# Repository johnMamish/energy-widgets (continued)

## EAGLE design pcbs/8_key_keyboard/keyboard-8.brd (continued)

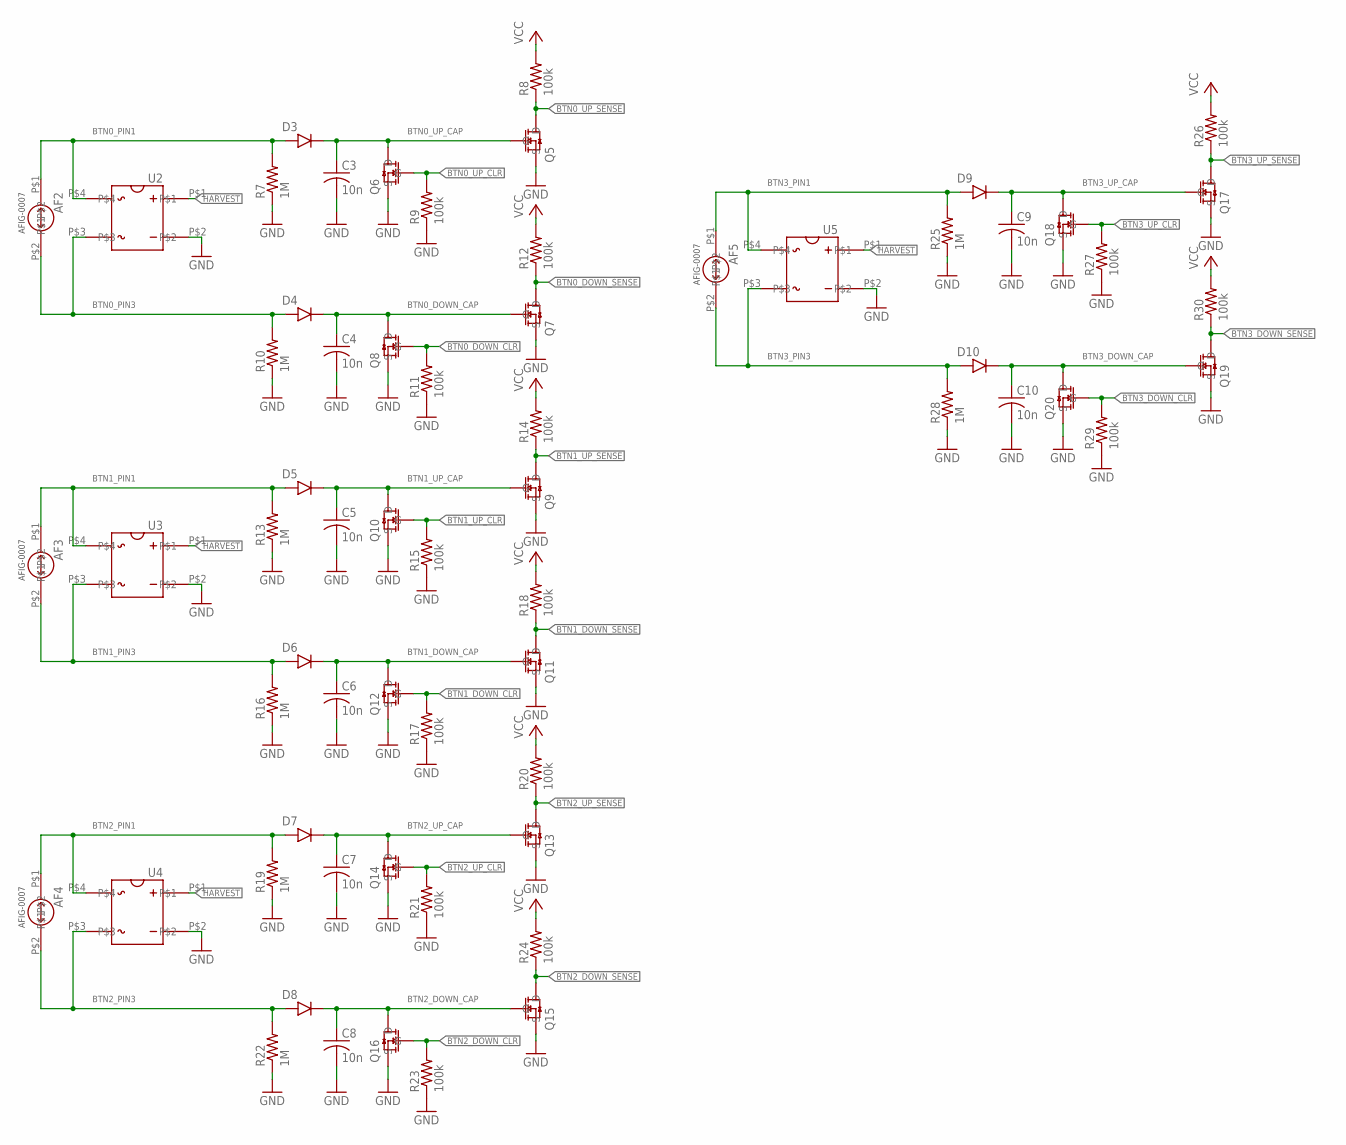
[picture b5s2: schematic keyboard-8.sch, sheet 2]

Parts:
AF2, AF3, AF4, AF5: BUTTON-MOUNT
C3, C4, C5, C6, C7, C8, C9, C10: 10n; C0402
D3, D4, D5, D6, D7, D8, D9, D10: DFLU1200
Q5, Q7, Q9, Q11, Q13, Q15, Q17, Q19: 2N7002K-7
Q6, Q8, Q10, Q12, Q14, Q16, Q18, Q20: BSS138K
R7, R10, R13, R16, R19, R22, R25, R28: 1M; R0402
R8, R9, R11, R12, R14, R15, R17, R18, R20, R21, R23, R24, R26, R27, R29, R30: 100k; R0402
U2, U3, U4, U5: CDBHD140L-G; CDBHDXX0L-G

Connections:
BTN0_DOWN_CAP: C4.1, D4.K, Q7.G, Q8.D
BTN0_DOWN_CLR: Q8.G, R11.2; also elsewhere on the board
BTN0_DOWN_SENSE: Q7.D, R12.1; also elsewhere on the board
BTN0_PIN1: AF2.P$1, D3.A, R7.2, U2.P$4
BTN0_PIN3: AF2.P$2, D4.A, R10.2, U2.P$3
BTN0_UP_CAP: C3.1, D3.K, Q5.G, Q6.D
BTN0_UP_CLR: Q6.G, R9.2; also elsewhere on the board
BTN0_UP_SENSE: Q5.D, R8.1; also elsewhere on the board
BTN1_DOWN_CAP: C6.1, D6.K, Q11.G, Q12.D
BTN1_DOWN_CLR: Q12.G, R17.2; also elsewhere on the board
BTN1_DOWN_SENSE: Q11.D, R18.1; also elsewhere on the board
BTN1_PIN1: AF3.P$1, D5.A, R13.2, U3.P$4
BTN1_PIN3: AF3.P$2, D6.A, R16.2, U3.P$3
BTN1_UP_CAP: C5.1, D5.K, Q9.G, Q10.D
BTN1_UP_CLR: Q10.G, R15.2; also elsewhere on the board
BTN1_UP_SENSE: Q9.D, R14.1; also elsewhere on the board
BTN2_DOWN_CAP: C8.1, D8.K, Q15.G, Q16.D
BTN2_DOWN_CLR: Q16.G, R23.2; also elsewhere on the board
BTN2_DOWN_SENSE: Q15.D, R24.1; also elsewhere on the board
BTN2_PIN1: AF4.P$1, D7.A, R19.2, U4.P$4
BTN2_PIN3: AF4.P$2, D8.A, R22.2, U4.P$3
BTN2_UP_CAP: C7.1, D7.K, Q13.G, Q14.D
BTN2_UP_CLR: Q14.G, R21.2; also elsewhere on the board
BTN2_UP_SENSE: Q13.D, R20.1; also elsewhere on the board
BTN3_DOWN_CAP: C10.1, D10.K, Q19.G, Q20.D
BTN3_DOWN_CLR: Q20.G, R29.2; also elsewhere on the board
BTN3_DOWN_SENSE: Q19.D, R30.1; also elsewhere on the board
BTN3_PIN1: AF5.P$1, D9.A, R25.2, U5.P$4
BTN3_PIN3: AF5.P$2, D10.A, R28.2, U5.P$3
BTN3_UP_CAP: C9.1, D9.K, Q17.G, Q18.D
BTN3_UP_CLR: Q18.G, R27.2; also elsewhere on the board
BTN3_UP_SENSE: Q17.D, R26.1; also elsewhere on the board
GND: C3.2, C4.2, C5.2, C6.2, C7.2, C8.2, C9.2, C10.2, Q5.S, Q6.S, Q7.S, Q8.S, Q9.S, Q10.S, Q11.S, Q12.S, Q13.S, Q14.S, Q15.S, Q16.S, Q17.S, Q18.S, Q19.S, Q20.S, R7.1, R9.1, R10.1, R11.1, R13.1, R15.1, R16.1, R17.1, R19.1, R21.1, R22.1, R23.1, R25.1, R27.1, R28.1, R29.1, U2.P$2, U3.P$2, U4.P$2, U5.P$2; also elsewhere on the board
HARVEST: U2.P$1, U3.P$1, U4.P$1, U5.P$1; also elsewhere on the board
VCC: R8.2, R12.2, R14.2, R18.2, R20.2, R24.2, R26.2, R30.2; also elsewhere on the board

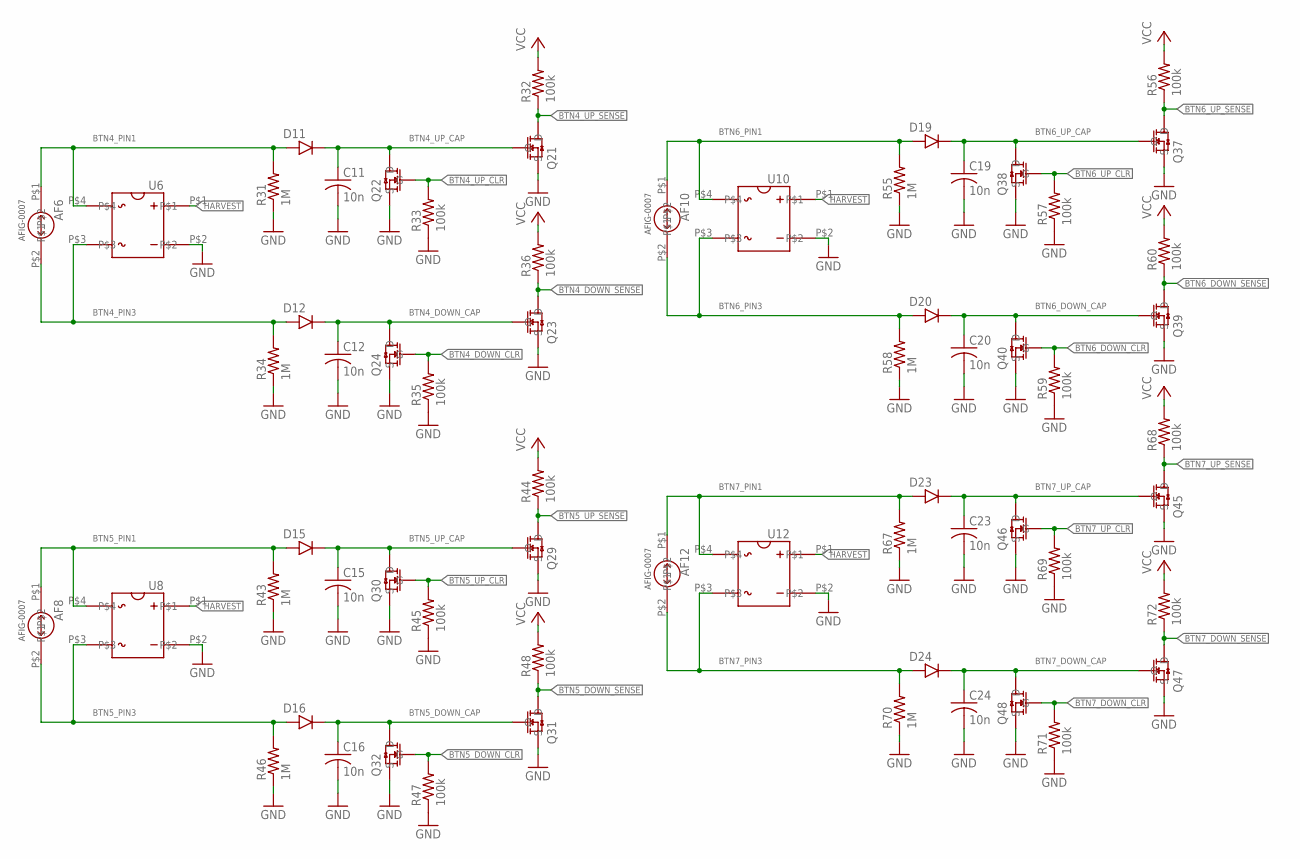
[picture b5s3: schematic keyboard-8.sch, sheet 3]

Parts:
AF6, AF8, AF10, AF12: BUTTON-MOUNT
C11, C12, C15, C16, C19, C20, C23, C24: 10n; C0402
D11, D12, D15, D16, D19, D20, D23, D24: DFLU1200
Q21, Q23, Q29, Q31, Q37, Q39, Q45, Q47: 2N7002K-7
Q22, Q24, Q30, Q32, Q38, Q40, Q46, Q48: BSS138K
R31, R34, R43, R46, R55, R58, R67, R70: 1M; R0402
R32, R33, R35, R36, R44, R45, R47, R48, R56, R57, R59, R60, R68, R69, R71, R72: 100k; R0402
U6, U8, U10, U12: CDBHD140L-G; CDBHDXX0L-G

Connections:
BTN4_DOWN_CAP: C12.1, D12.K, Q23.G, Q24.D
BTN4_DOWN_CLR: Q24.G, R35.2; also elsewhere on the board
BTN4_DOWN_SENSE: Q23.D, R36.1; also elsewhere on the board
BTN4_PIN1: AF6.P$1, D11.A, R31.2, U6.P$4
BTN4_PIN3: AF6.P$2, D12.A, R34.2, U6.P$3
BTN4_UP_CAP: C11.1, D11.K, Q21.G, Q22.D
BTN4_UP_CLR: Q22.G, R33.2; also elsewhere on the board
BTN4_UP_SENSE: Q21.D, R32.1; also elsewhere on the board
BTN5_DOWN_CAP: C16.1, D16.K, Q31.G, Q32.D
BTN5_DOWN_CLR: Q32.G, R47.2; also elsewhere on the board
BTN5_DOWN_SENSE: Q31.D, R48.1; also elsewhere on the board
BTN5_PIN1: AF8.P$1, D15.A, R43.2, U8.P$4
BTN5_PIN3: AF8.P$2, D16.A, R46.2, U8.P$3
BTN5_UP_CAP: C15.1, D15.K, Q29.G, Q30.D
BTN5_UP_CLR: Q30.G, R45.2; also elsewhere on the board
BTN5_UP_SENSE: Q29.D, R44.1; also elsewhere on the board
BTN6_DOWN_CAP: C20.1, D20.K, Q39.G, Q40.D
BTN6_DOWN_CLR: Q40.G, R59.2; also elsewhere on the board
BTN6_DOWN_SENSE: Q39.D, R60.1; also elsewhere on the board
BTN6_PIN1: AF10.P$1, D19.A, R55.2, U10.P$4
BTN6_PIN3: AF10.P$2, D20.A, R58.2, U10.P$3
BTN6_UP_CAP: C19.1, D19.K, Q37.G, Q38.D
BTN6_UP_CLR: Q38.G, R57.2; also elsewhere on the board
BTN6_UP_SENSE: Q37.D, R56.1; also elsewhere on the board
BTN7_DOWN_CAP: C24.1, D24.K, Q47.G, Q48.D
BTN7_DOWN_CLR: Q48.G, R71.2; also elsewhere on the board
BTN7_DOWN_SENSE: Q47.D, R72.1; also elsewhere on the board
BTN7_PIN1: AF12.P$1, D23.A, R67.2, U12.P$4
BTN7_PIN3: AF12.P$2, D24.A, R70.2, U12.P$3
BTN7_UP_CAP: C23.1, D23.K, Q45.G, Q46.D
BTN7_UP_CLR: Q46.G, R69.2; also elsewhere on the board
BTN7_UP_SENSE: Q45.D, R68.1; also elsewhere on the board
GND: C11.2, C12.2, C15.2, C16.2, C19.2, C20.2, C23.2, C24.2, Q21.S, Q22.S, Q23.S, Q24.S, Q29.S, Q30.S, Q31.S, Q32.S, Q37.S, Q38.S, Q39.S, Q40.S, Q45.S, Q46.S, Q47.S, Q48.S, R31.1, R33.1, R34.1, R35.1, R43.1, R45.1, R46.1, R47.1, R55.1, R57.1, R58.1, R59.1, R67.1, R69.1, R70.1, R71.1, U6.P$2, U8.P$2, U10.P$2, U12.P$2; also elsewhere on the board
HARVEST: U6.P$1, U8.P$1, U10.P$1, U12.P$1; also elsewhere on the board
VCC: R32.2, R36.2, R44.2, R48.2, R56.2, R60.2, R68.2, R72.2; also elsewhere on the board

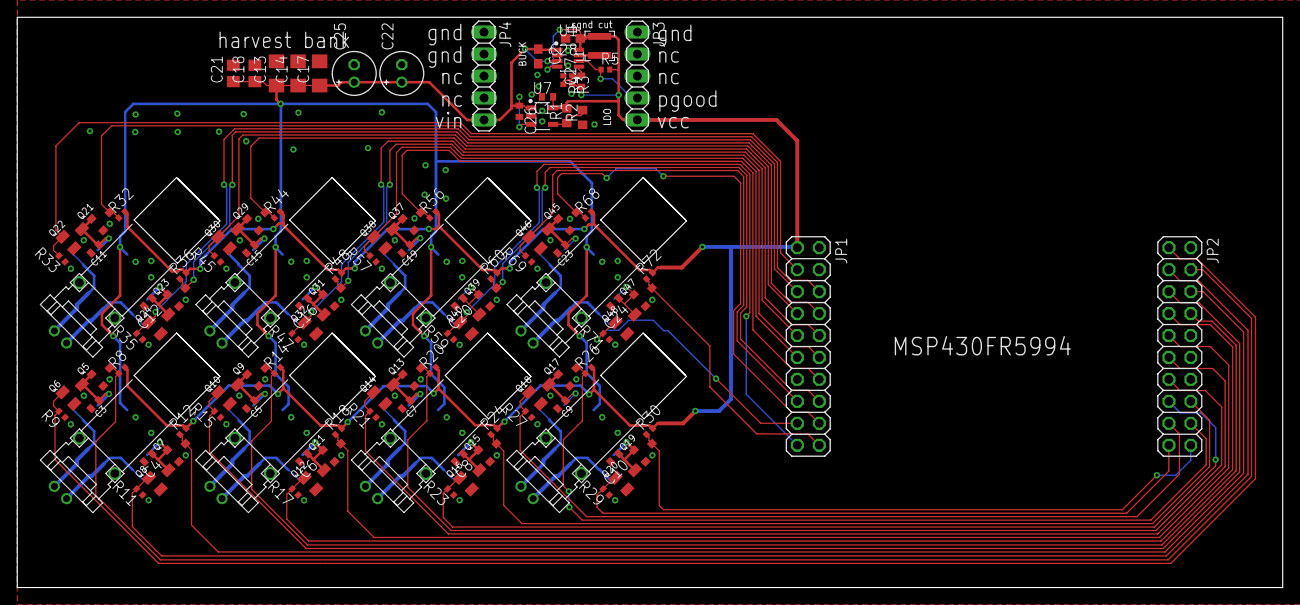
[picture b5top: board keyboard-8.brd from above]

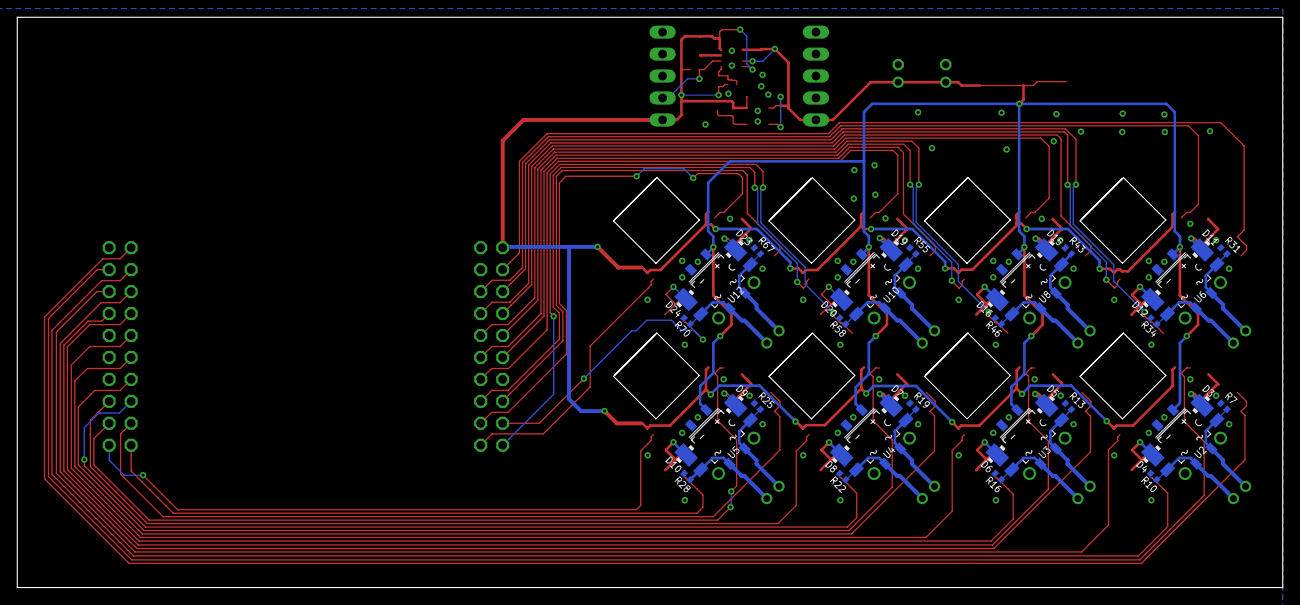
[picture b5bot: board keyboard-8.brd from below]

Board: 2 copper layers, 146.5 x 66.0 mm, 152 parts (40 on the bottom side), 71 nets.

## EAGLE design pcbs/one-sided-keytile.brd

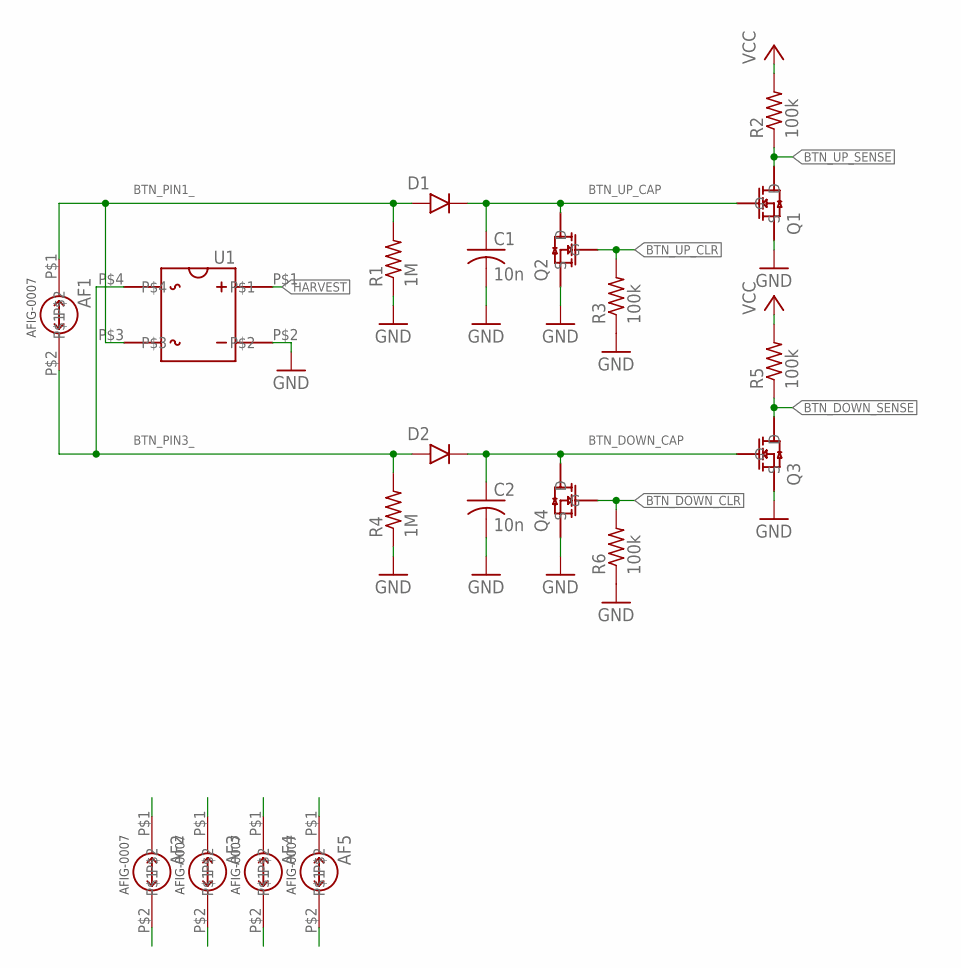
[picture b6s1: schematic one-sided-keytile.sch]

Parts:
AF1, AF2, AF3, AF4, AF5: BUTTON-MOUNT
C1, C2: 10n; C0402
D1, D2: DFLU1200
Q1, Q3: 2N7002K-7
Q2, Q4: BSS138K
R1, R4: 1M; R0402
R2, R3, R5, R6: 100k; R0402
U1: CDBHD140L-G; CDBHDXX0L-G

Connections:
BTN_DOWN_CAP: C2.1, D2.K, Q3.G, Q4.D
BTN_DOWN_CLR: Q4.G, R6.2
BTN_DOWN_SENSE: Q3.D, R5.1
BTN_PIN1_: AF1.P$1, D1.A, R1.2, U1.P$3
BTN_PIN1_1: AF2.P$1
BTN_PIN1_2: AF3.P$1
BTN_PIN1_3: AF4.P$1
BTN_PIN1_4: AF5.P$1
BTN_PIN3_: AF1.P$2, D2.A, R4.2, U1.P$4
BTN_PIN3_1: AF2.P$2
BTN_PIN3_2: AF3.P$2
BTN_PIN3_3: AF4.P$2
BTN_PIN3_4: AF5.P$2
BTN_UP_CAP: C1.1, D1.K, Q1.G, Q2.D
BTN_UP_CLR: Q2.G, R3.2
BTN_UP_SENSE: Q1.D, R2.1
GND: C1.2, C2.2, Q1.S, Q2.S, Q3.S, Q4.S, R1.1, R3.1, R4.1, R6.1, U1.P$2
HARVEST: U1.P$1
VCC: R2.2, R5.2

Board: 2 copper layers, 20 parts (0 on the bottom side), 10 nets, no tracks yet.

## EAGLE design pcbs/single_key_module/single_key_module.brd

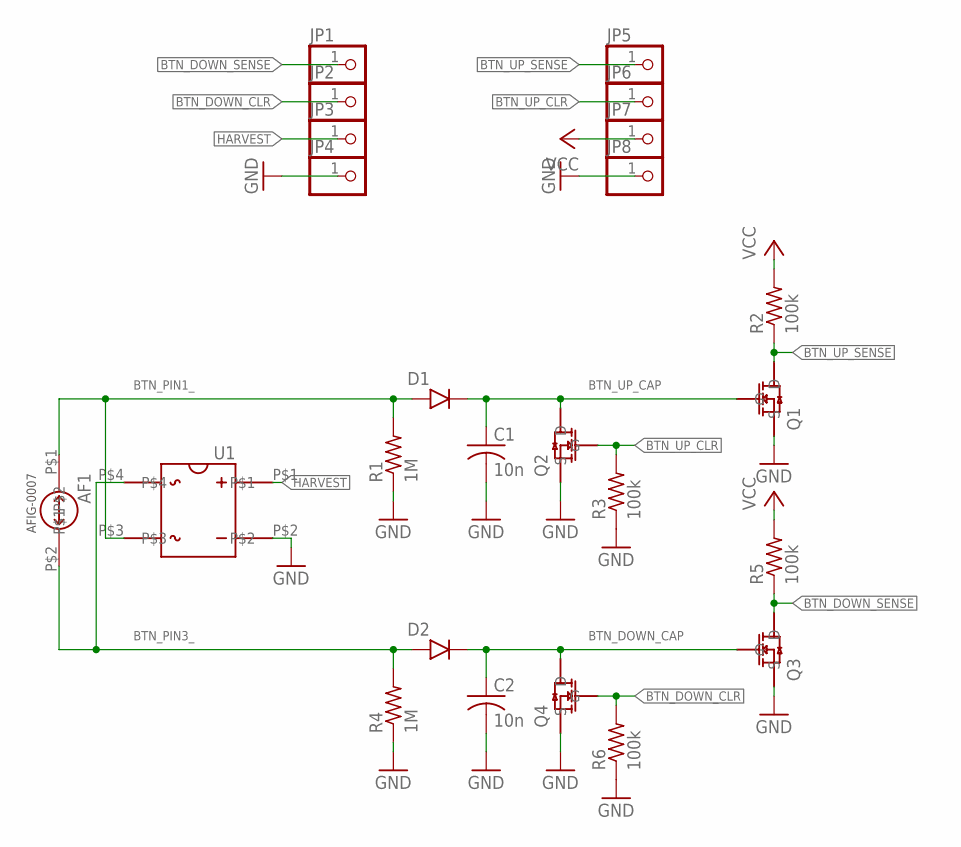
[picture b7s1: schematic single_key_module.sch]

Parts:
AF1: BUTTON-MOUNT
C1, C2: 10n; C0402
D1, D2: DFLU1200
JP1, JP2, JP3, JP4, JP5, JP6, JP7, JP8: PINHD-1X1; 1X01
Q1, Q3: 2N7002K-7
Q2, Q4: BSS138K
R1, R4: 1M; R0402
R2, R3, R5, R6: 100k; R0402
U1: CDBHD140L-G; CDBHDXX0L-G

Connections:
BTN_DOWN_CAP: C2.1, D2.K, Q3.G, Q4.D
BTN_DOWN_CLR: JP2.1, Q4.G, R6.2
BTN_DOWN_SENSE: JP1.1, Q3.D, R5.1
BTN_PIN1_: AF1.P$1, D1.A, R1.2, U1.P$3
BTN_PIN3_: AF1.P$2, D2.A, R4.2, U1.P$4
BTN_UP_CAP: C1.1, D1.K, Q1.G, Q2.D
BTN_UP_CLR: JP6.1, Q2.G, R3.2
BTN_UP_SENSE: JP5.1, Q1.D, R2.1
GND: C1.2, C2.2, JP4.1, JP8.1, Q1.S, Q2.S, Q3.S, Q4.S, R1.1, R3.1, R4.1, R6.1, U1.P$2
HARVEST: JP3.1, U1.P$1
VCC: JP7.1, R2.2, R5.2

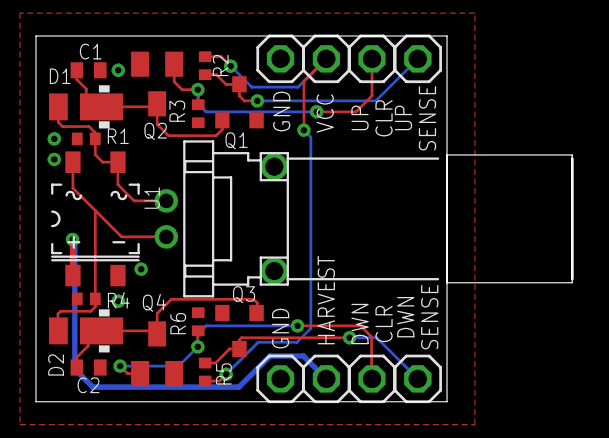
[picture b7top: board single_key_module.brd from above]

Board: 2 copper layers, 29.8 x 20.3 mm, 24 parts (0 on the bottom side), 11 nets.

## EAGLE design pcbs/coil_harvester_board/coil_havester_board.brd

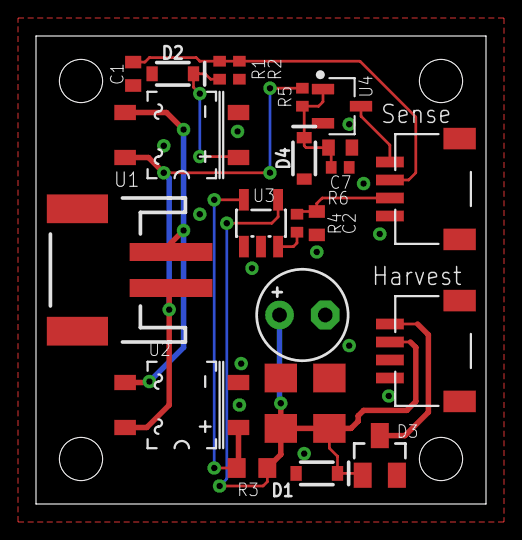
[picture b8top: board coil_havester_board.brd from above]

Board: 2 copper layers, 25.0 x 26.0 mm, 23 parts (0 on the bottom side), 12 nets.

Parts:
C1, C2: 1n; C0402
C3, C4: C1206
C5: DNP; E2,5-5
C7: 10n; C0402
D1, D2, D4: 3.3V; SOD-323
D3: BAT54; SOT23
J1: JST-2-SMD
JP2, JP3: JST-SH-4
R1: 1M 1%; R0402
R2, R4: 150k 1%; R0402
R3: 3.3 1%; R0603
R5: 10k; R0402
R6: 150K 1%; R0402
U1, U2: CDBHD140L-G; CDBHDXX0L-G
U3: MAX9938; SOT23-5
U4: TN2106K1-G

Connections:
DIRSENSE: JP3.4, U4.D
GND: C1.2, C2.2, C3.2, C4.2, C5.-, C7.2, D1.A, D2.A, D4.A, JP2.1, JP2.2, JP3.1, R2.1, R6.1, U1.P$2, U2.P$2, U3.1, U3.2, U4.S
ISENSE: C2.1, JP3.2, R4.1
unnamed: J1.1, R5.2, U1.P$4, U2.P$4
unnamed: J1.2, U1.P$3, U2.P$3
unnamed: D2.C, R1.2, U1.P$1
unnamed: R3.1, U2.P$1, U3.5
unnamed: R4.2, U3.3
unnamed: C7.1, D4.C, R5.1, R6.2, U4.G
VHARVEST: C3.1, C4.1, C5.+, D1.C, D3.1, JP2.3, R3.2, U3.4
VHARVEST_R: D3.3, JP2.4
VSENSE: C1.1, JP3.3, R1.1, R2.2

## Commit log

2020-10-14 add first rev of PCBs for energy harvesting buttons and keyboard
2020-10-14 README and gitignore
2020-10-14 add some data traces collected from afig-0007 buttons
2020-10-14 add demo keyboard firmware that reads button presses
2020-10-14 start on battery-free bop-it
2020-10-15 bringup DMA
2020-10-15 add some tools for converting audio files to C source code
2020-10-15 add some binary wav files
2020-10-15 fix bad C in audio_to_header script
2020-10-15 dma-driven PWM passes smoke test
2020-10-15 update code so 20-bit addrs are correctly written to DMA regs
2020-10-16 remove some cruft from main
2020-10-16 add some wav assets
2020-10-16 fix some C issues with audio_to_header
2020-10-16 add random sample selection example to main.c
2020-10-19 added peppermill board, ready to order
2020-10-22 add 3 pcbs that (should) be ready for manufacture
2020-10-22 add bop-it mechanical cutout
2020-10-22 fix issue with audio header conversion; allow overlapping audio
2020-11-02 ADC initialization wip
2020-11-02 add jupyter notebook for looking at energy traces for motor and flashlight
2020-11-02 change some filepaths in jupyter notebook for button press data analysis
2020-11-03 adc readings wip
2020-11-05 ADC is timer triggered
2020-11-05 get CPU to enter low-power mode and validate power savings with keithley sourcemeter
2020-11-11 add some notes to firmware README
2020-11-11 update gitignores
2020-11-11 add cam file for coil harvester board
2020-11-12 spice model for harvesting system wip
2020-11-12 add power integration to get total harvested energy
2020-11-12 hack to remove discontinuity from I_sys allows simulation to converge
2020-11-12 improve discontinuity management in Isys
2020-11-12 add some loop sanity checks to find bug in ngspice27, fixed in 33
2020-11-13 add fixed-point calcs for open-circuit voltage
2020-11-13 constant current model works with ngspice33
2020-11-14 add diode model for CDBHD140L-G rectifier
2020-11-14 game logic wip
2020-11-17 game logic compiles, testing WIP
2020-11-18 fix audio dma bug
2020-11-18 game debugging wip
2020-11-18 bopit works with twist only
2020-11-18 shake and twist work; needs a lot of force for shake
2020-11-18 fix small typo in audio-to-header tool
2021-01-08 artemis board wip
2021-01-13 artemis energy harvesting board ready for ordering
2021-02-15 move files to subdir to add other microcontroller
2021-02-15 add samd21 code wip
2021-02-15 change audio-to-header script to remove weird arm-ld linker errors when putting arrays in .upper.rodata
2021-02-15 samd21 plays noises
2021-02-17 fix inconsistent sample rate on ADC
2021-03-05 Create saleae_csv_parse
2022-01-25 Squashed 'firmware/external/saeclib/' content from commit dfa403a
    git-subtree-dir: firmware/external/saeclib
    git-subtree-split: dfa403aeaa6d197b81bfb1e4836d50b807dcd877
2022-01-31 simon says WIP
2022-02-02 add bandlimited square wave generation tool I found online
2022-02-04 simon says passes smoke test
2022-02-04 remove unnecessary DMA init from simon says
2022-02-05 add "happy-or-not" customer rating demo
2022-02-08 etch-a-sketch firmware wip; spi works
2022-02-09 bouncing line demo works
2022-02-11 etch-a-sketch app passes smoke test
